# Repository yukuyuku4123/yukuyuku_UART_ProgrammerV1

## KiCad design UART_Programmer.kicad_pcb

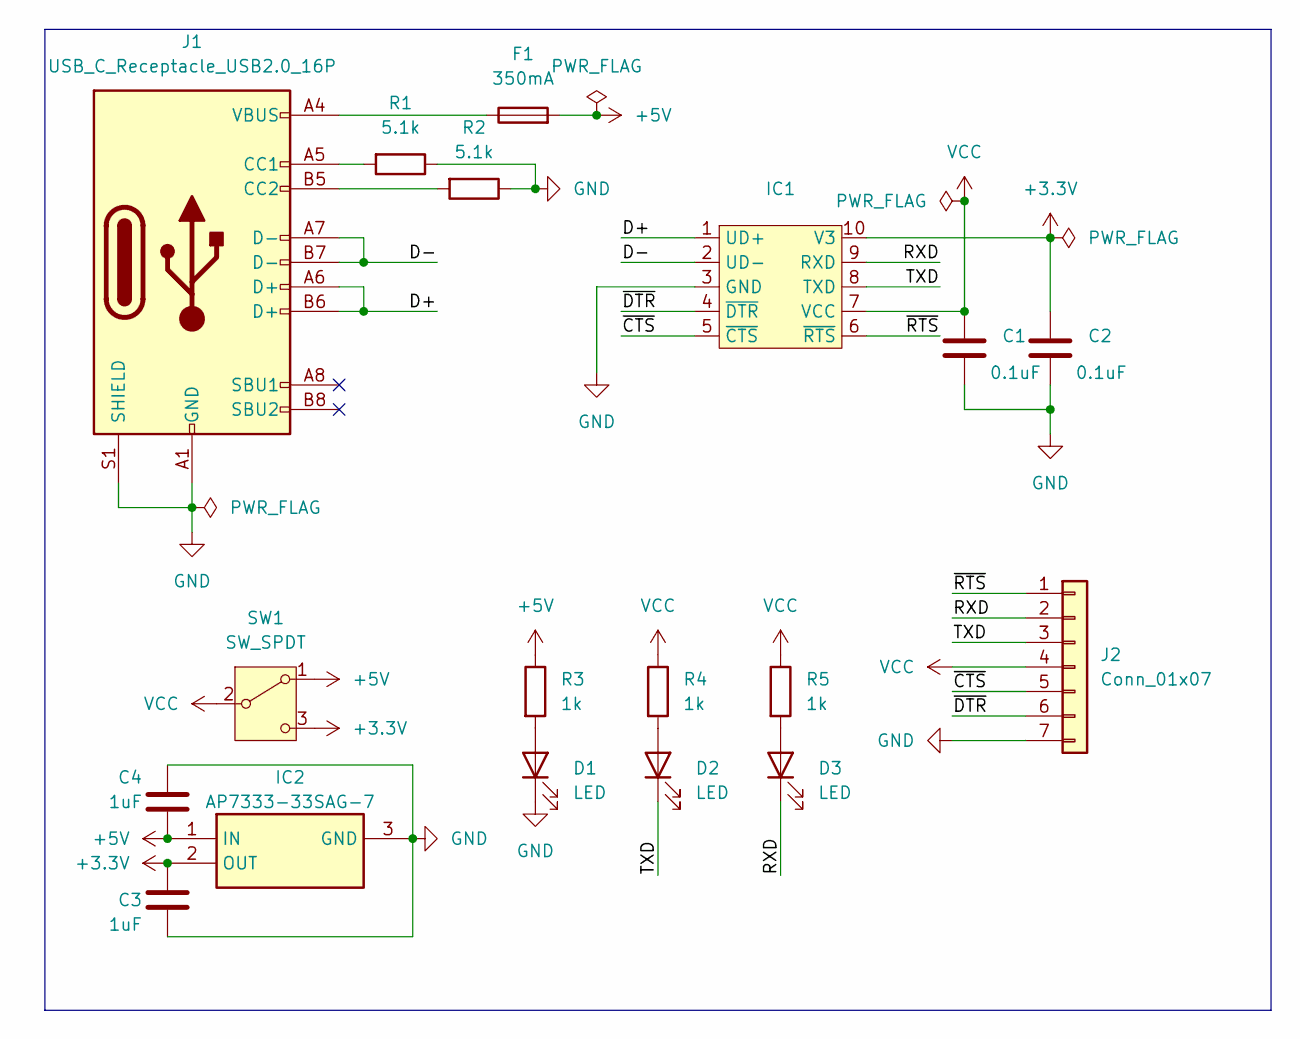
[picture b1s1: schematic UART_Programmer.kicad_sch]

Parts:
C1, C2: 0.1uF; C_0402_1005Metric
C3, C4: 1uF; C_0603_1608Metric
D1, D2, D3: LED; LED_0603_1608Metric
F1: 350mA; Fuse_0402_1005Metric
IC1: SSOP-10_3.9x4.9mm_P1.00mm
IC2: AP7333-33SAG-7; TSOT-23; Mouser Part Number 621-AP7333-33SAG-7
J1: USB_C_Receptacle_USB2.0_16P; USB_C_Receptacle_GCT_USB4105-xx-A_16P_TopMnt_Horizontal
J2: Conn_01x07; PinHeader_1x07_P2.54mm_Vertical
R1, R2: 5.1k; R_0603_1608Metric
R3, R4, R5: 1k; R_0603_1608Metric
SW1: SW_SPDT; SW_Slide_SPDT_Angled_CK_OS102011MA1Q

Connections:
+3.3V: C2.1, C3.1, IC1.10 (V3), IC2.2 (OUT), SW1.3 (C)
+5V: C4.2, F1.2, IC2.1 (IN), R3.1, SW1.1 (A)
/D+: IC1.1 (UD+), J1.A6 (D+), J1.B6 (D+)
/D-: IC1.2 (UD-), J1.A7 (D-), J1.B7 (D-)
/RXD: D3.1 (K), IC1.9 (RXD), J2.2
/TXD: D2.1 (K), IC1.8 (TXD), J2.3
/~CTS: IC1.5 (~CTS), J2.5
/~DTR: IC1.4 (~DTR), J2.6
/~RTS: IC1.6 (~RTS), J2.1
GND: C1.2, C2.2, C3.2, C4.1, D1.1 (K), IC1.3 (GND), IC2.3 (GND), J1.A1 (GND), J1.A12 (GND), J1.B1 (GND), J1.B12 (GND), J1.S1 (SHIELD), J2.7, R1.1, R2.1
unnamed: D1.2 (A), R3.2
unnamed: D2.2 (A), R4.2
unnamed: D3.2 (A), R5.2
unnamed: F1.1, J1.A4 (VBUS), J1.A9 (VBUS), J1.B4 (VBUS), J1.B9 (VBUS)
unnamed: J1.A5 (CC1), R1.2
unnamed: J1.B5 (CC2), R2.2
VCC: C1.1, IC1.7 (VCC), J2.4, R4.1, R5.1, SW1.2 (B)

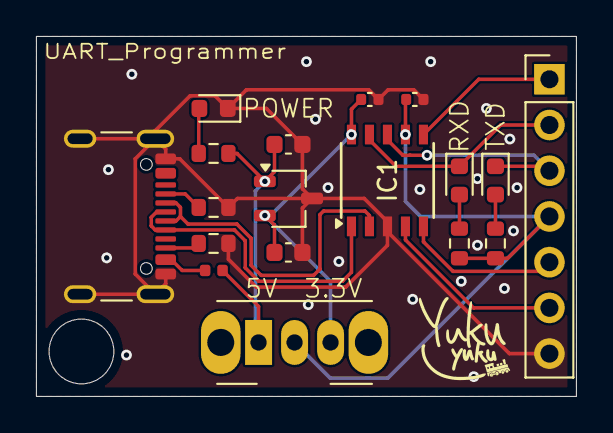
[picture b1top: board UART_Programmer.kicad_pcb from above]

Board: 2 copper layers, 30.0 x 20.0 mm, 18 parts (0 on the bottom side), 17 nets.

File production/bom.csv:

Designator,Footprint,Quantity,Value,LCSC Part #
"C1, C2",0402,2,0.1uF,
"C3, C4",0603,2,1uF,
"D1, D2, D3",0603,3,LED,
F1,0402,1,350mA,
IC1,SSOP-10_3.9x4.9mm_P1.00mm,1,~,
IC2,TSOT-23,1,AP7333-33SAG-7,
J1,USB_C_Receptacle_GCT_USB4105-xx-A_16P_TopMnt_Horizontal,1,USB_C_Receptacle_USB2.0_16P,
J2,PinHeader_1x07_P2.54mm_Vertical,1,Conn_01x07,
"R1, R2",0603,2,5.1k,
"R3, R4, R5",0603,3,1k,
SW1,SW_Slide_SPDT_Angled_CK_OS102011MA1Q,1,SW_SPDT,

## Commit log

2024-07-27 Ver-1.0
2024-07-27 Create LICENSE
2024-07-27 Update LICENSE
